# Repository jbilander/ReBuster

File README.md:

# ReBuster
A drop-in replacement PCB for the Amiga Super Buster chip

This is WORK IN PROGRESS. If you generate gerbers and order PCBs from this source you are doing so completely at your own risk!.

***

***

<br />

<br />

***

***

BOM Rev. 2A
---------
Reference  | Name/Value   | Package | Notes
-|-|-|-|
U1 | 10M04SCU169C8G  | BGA-169 11.0x11.0mm_Layout13x13 | Max 10 FPGA [10M04SCU169C8G](https://www.mouser.com/ProductDetail/989-10M04SCU169C8G)
U2 | LM1117-3.3 | SOT-223 | Low-Dropout Linear Regulator 3.3 Volt
U3,U5,U6 | SN74CBTD16210 | TSSOP-48 6.1x12.5mm_P0.5mm | 20-BIT FET Bus switch with level shifting, high-speed TTL-compatible. [74CBTD16210DGGR](https://www.mouser.com/ProductDetail/595-74CBTD16210DGGR)
U4 | SN74LVC16245ADGVR | TSSOP-48_4.4x9.7mm_P0.4mm | 16-bit (dual-octal) noninverting bus transceiver [SN74LVC16245ADGVR](https://www.mouser.com/ProductDetail/595-SNLVC16245ADGVR)
U7 | 74LVC2G07GV | TSOP-6_1.65x3.05mm_P0.95mm | Open Drain noninverting line driver [74LVC2G07GV](https://www.mouser.com/ProductDetail/771-LVC2G07GV125)
U8 | Winslow PLCC-84 Plug | PLCC-84 Plug | Optionally use a home made plug (stacked PCBs)
U9 | PLCC-84_TH_pin_holes | TH_plug_pins | Pins that could be used with the DIY-plug PCBs rev1d for manual fitting, L8.7mm [Aliexpress](https://www.aliexpress.com/item/32893608810.html).
RN1, RN2 | CAY16-1002F4LF RES ARRAY 4 Resistors 10k Ω | 1206 | [CAY16-1002F4LF](https://www.mouser.com/ProductDetail/652-CAY16-1002F4LF)
C1-3 | Capacitor 10uF | 1206 | 
C4,C5,C8,C11 | Capacitor 1uF | 0805 | 
C6,C7,C9,C10 | Capacitor 0.1uF = 100nF | 0805 | 
C12-C19, C21-C23 | Capacitor 0.01uF = 10nF | 0603 |
C20, C24-C28 | Capacitor 0.1uF = 100nF | 0603 |
JTAG | SMT Pin Header Male | SMT 2 x 5 Pin 2.0mm pitch |

***

***

***

BOM Rev. 1A
---------
Reference  | Name/Value   | Package | Notes
-|-|-|-|
U1 | GW1N-UV9UG169C6/I5  | BGA-169 11.0x11.0mm_Layout13x13 | Gowin FPGA [GW1N-UV9UG169](https://www.mouser.com/ProductDetail/192-GW1NUV9UG169C6I5)
U2 | LM1117-3.3 | SOT-223 | Low-Dropout Linear Regulator 3.3 Volt
U3-U6 | SN74CBTD16210 | TSSOP-48 6.1x12.5mm_P0.5mm | 20-BIT FET Bus switch with level shifting, high-speed TTL-compatible. [74CBTD16210DGGR](https://www.mouser.com/ProductDetail/595-74CBTD16210DGGR)
U7 | Winslow PLCC-84 Plug | PLCC-84 Plug | Optionally use a home made plug (stacked PCBs)
U8 | PLCC-84_TH_pin_holes | TH_plug_pins | Pins that could be used with the DIY-plug PCBs rev1d for manual fitting, L8.7mm [Aliexpress](https://www.aliexpress.com/item/32893608810.html).
RN1, RN2 | CAY16A-4701F4LF RES ARRAY 4 Resistors 4.7k Ω | 1206 | [CAY16A-4701F4LF](https://wwww.mouser.com/ProductDetail/652-CAY16A-4701F4LF)
C1-3 | Capacitor 10uF | 1206 | 
C4,C5,C8,C11 | Capacitor 1uF | 0805 | 
C6,C7,C9,C10 | Capacitor 0.1uF = 100nF | 0805 | 
C12-C19 | Capacitor 0.01uF = 10nF | 0603 |
C20 | Capacitor 0.1uF = 100nF | 0603 |
C21-C24 | Capacitor 0.01uF = 10nF | 0603 |
JTAG | SMT Pin Header Male | SMT 2 x 5 Pin 2.0mm pitch |

***

When ordering from JLCPCB select:

Specify Layer Sequence: Yes

    L1(Top layer):    F_Cu.gbr
    L2(Inner layer1): GND_Cu.gbr
    L3(Inner layer2): VCC_Cu.gbr
    L4(Bottom layer): B_Cu.gbr

Remove Order Number: 

    Specify a location

This will notify JLC where to put the order number, they will replace the "JLCJLCJLCJLC" silkscreen label.

***

[![CC BY-SA 4.0][cc-by-sa-shield]][cc-by-sa]

This work is licensed under a
[Creative Commons Attribution-ShareAlike 4.0 International License][cc-by-sa].

[![CC BY-SA 4.0][cc-by-sa-image]][cc-by-sa]

[cc-by-sa]: http://creativecommons.org/licenses/by-sa/4.0/
[cc-by-sa-image]: https://licensebuttons.net/l/by-sa/4.0/88x31.png
[cc-by-sa-shield]: https://img.shields.io/badge/License-CC%20BY--SA%204.0-lightgrey.svg

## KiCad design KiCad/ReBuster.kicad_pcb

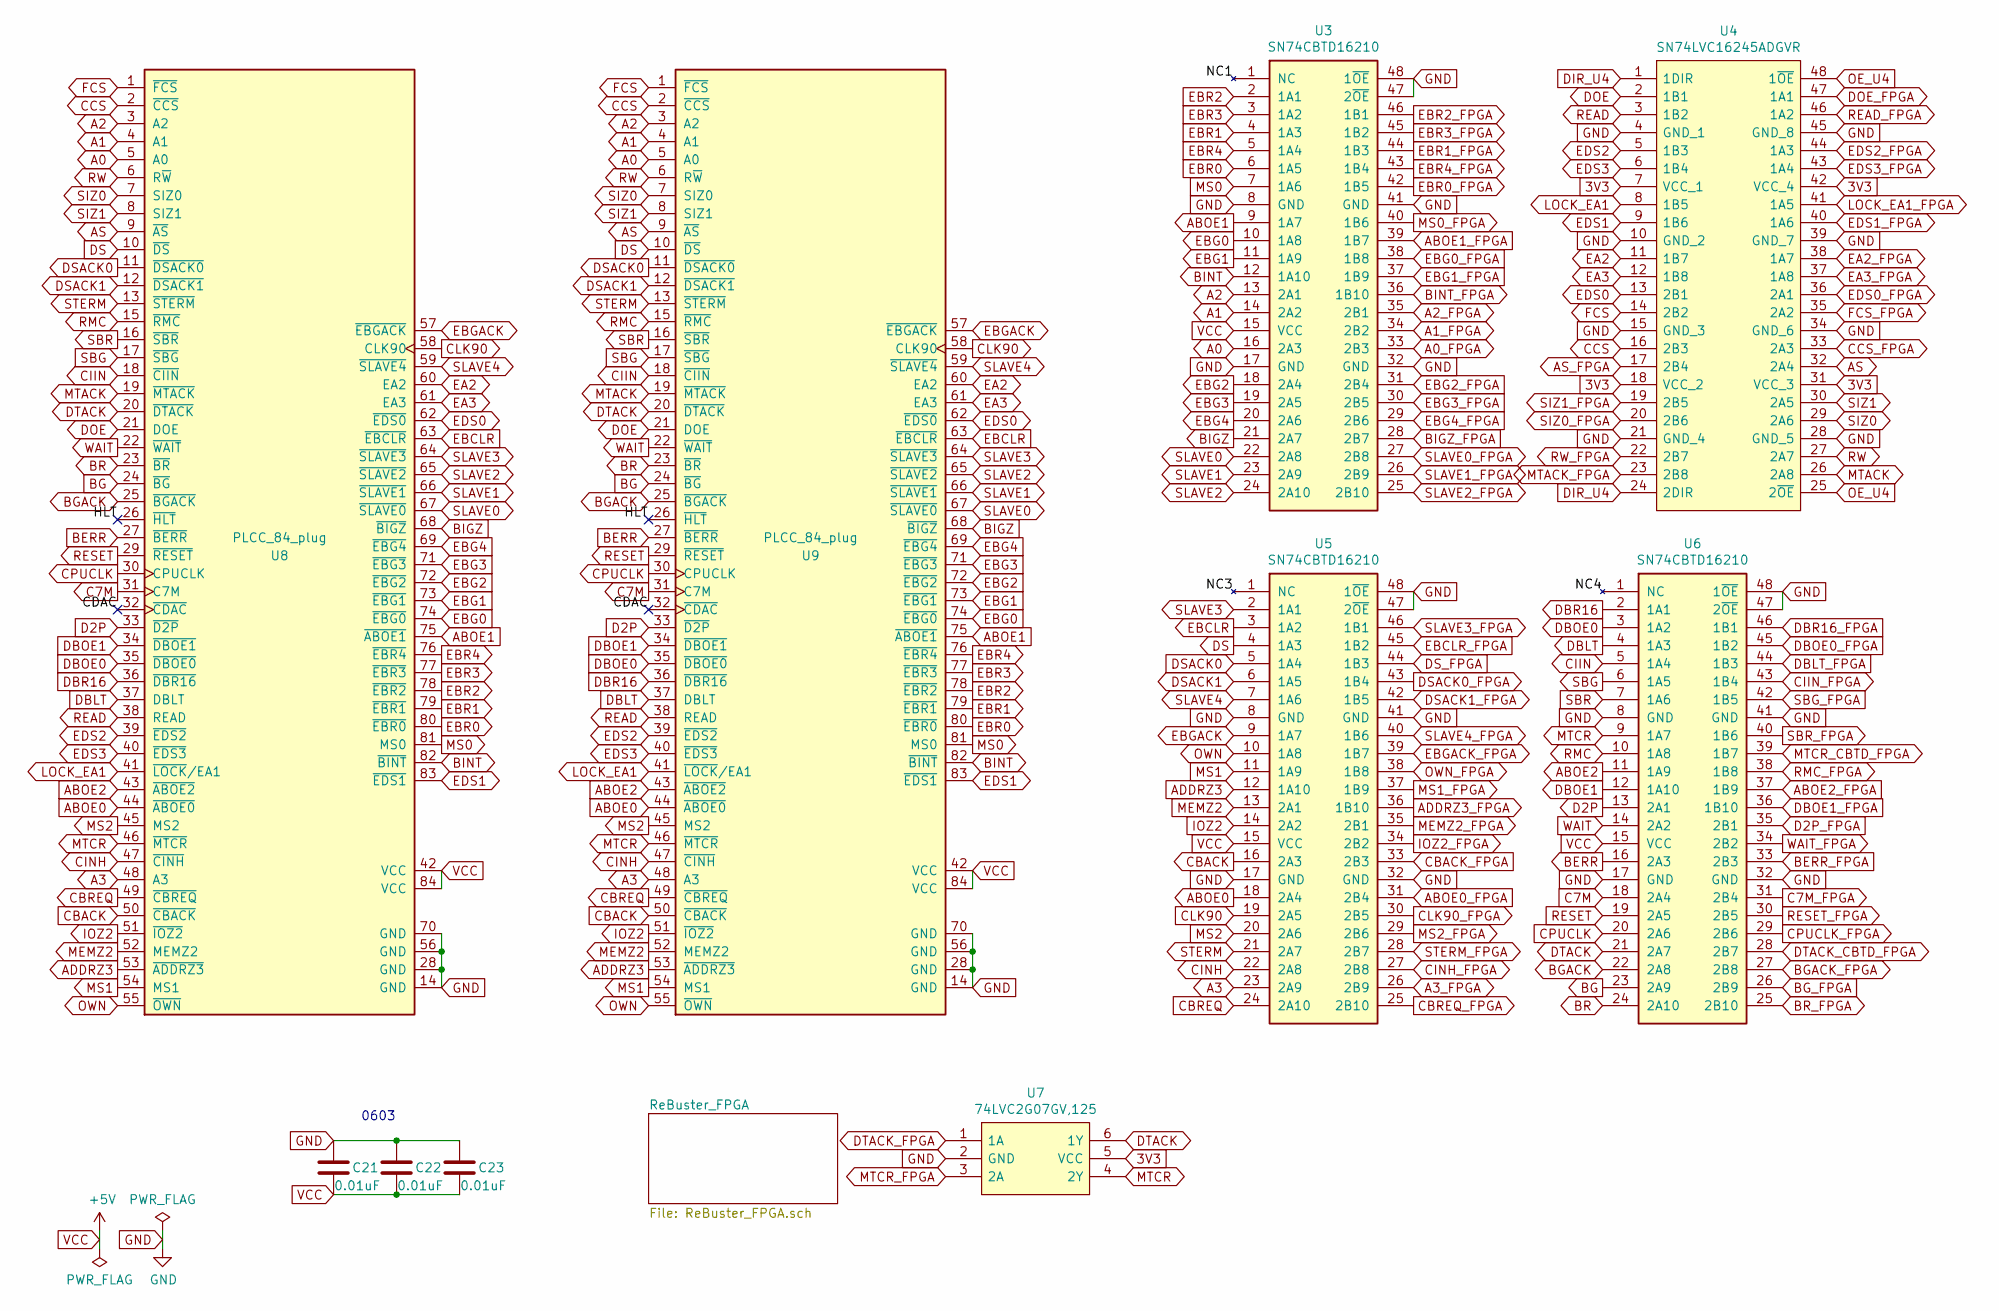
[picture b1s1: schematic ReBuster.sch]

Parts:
C21, C22, C23: 0.01uF; C_0603_1608Metric_Pad1.05x0.95mm_HandSolder
U3, U5, U6: SN74CBTD16210; TSSOP-48_6.1x12.5mm_P0.5mm_padLength_1mm
U4: SN74LVC16245ADGVR; TSSOP-48_4.4x9.7mm_P0.4mm_custom
U7: 74LVC2G07GV,125; TSOP-6_1.65x3.05mm_P0.95mm
U8: PLCC_84_plug; PLCC-84_Plug_P1.27mm_mirrored
U9: PLCC_84_plug; PLCC-84_TH_pin_holes

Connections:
3V3: U4.7 (VCC_1), U4.18 (VCC_2), U4.31 (VCC_3), U4.42 (VCC_4), U7.5 (VCC); also elsewhere on the board
/CDAC: U8.32 (~CDAC), U9.32 (~CDAC)
/HLT: U8.26 (~HLT), U9.26 (~HLT)
/NC1: U3.1 (NC)
/NC3: U5.1 (NC)
/NC4: U6.1 (NC)
A0: U3.16 (2A3), U8.5 (A0), U9.5 (A0)
A0_FPGA: U3.33 (2B3); also elsewhere on the board
A1: U3.14 (2A2), U8.4 (A1), U9.4 (A1)
A1_FPGA: U3.34 (2B2); also elsewhere on the board
A2: U3.13 (2A1), U8.3 (A2), U9.3 (A2)
A2_FPGA: U3.35 (2B1); also elsewhere on the board
A3: U5.23 (2A9), U8.48 (A3), U9.48 (A3)
A3_FPGA: U5.26 (2B9); also elsewhere on the board
ABOE0: U5.18 (2A4), U8.44 (~ABOE0), U9.44 (~ABOE0)
ABOE0_FPGA: U5.31 (2B4); also elsewhere on the board
ABOE1: U3.9 (1A7), U8.75 (~ABOE1), U9.75 (~ABOE1)
ABOE1_FPGA: U3.39 (1B7); also elsewhere on the board
ABOE2: U6.11 (1A9), U8.43 (~ABOE2), U9.43 (~ABOE2)
ABOE2_FPGA: U6.37 (1B9); also elsewhere on the board
ADDRZ3: U5.12 (1A10), U8.53 (~ADDRZ3), U9.53 (~ADDRZ3)
ADDRZ3_FPGA: U5.36 (1B10); also elsewhere on the board
AS: U4.32 (2A4), U8.9 (~AS), U9.9 (~AS)
AS_FPGA: U4.17 (2B4); also elsewhere on the board
BERR: U6.16 (2A3), U8.27 (~BERR), U9.27 (~BERR)
BERR_FPGA: U6.33 (2B3); also elsewhere on the board
BG: U6.23 (2A9), U8.24 (~BG), U9.24 (~BG)
BGACK: U6.22 (2A8), U8.25 (~BGACK), U9.25 (~BGACK)
BGACK_FPGA: U6.27 (2B8); also elsewhere on the board
BG_FPGA: U6.26 (2B9); also elsewhere on the board
BIGZ: U3.21 (2A7), U8.68 (~BIGZ), U9.68 (~BIGZ)
BIGZ_FPGA: U3.28 (2B7); also elsewhere on the board
BINT: U3.12 (1A10), U8.82 (~BINT), U9.82 (~BINT)
BINT_FPGA: U3.36 (1B10); also elsewhere on the board
BR: U6.24 (2A10), U8.23 (~BR), U9.23 (~BR)
BR_FPGA: U6.25 (2B10); also elsewhere on the board
C7M: U6.18 (2A4), U8.31 (C7M), U9.31 (C7M)
C7M_FPGA: U6.31 (2B4); also elsewhere on the board
CBACK: U5.16 (2A3), U8.50 (~CBACK), U9.50 (~CBACK)
CBACK_FPGA: U5.33 (2B3); also elsewhere on the board
CBREQ: U5.24 (2A10), U8.49 (~CBREQ), U9.49 (~CBREQ)
CBREQ_FPGA: U5.25 (2B10); also elsewhere on the board
CCS: U4.16 (2B3), U8.2 (~CCS), U9.2 (~CCS)
CCS_FPGA: U4.33 (2A3); also elsewhere on the board
CIIN: U6.5 (1A4), U8.18 (~CIIN), U9.18 (~CIIN)
CIIN_FPGA: U6.43 (1B4); also elsewhere on the board
CINH: U5.22 (2A8), U8.47 (~CINH), U9.47 (~CINH)
CINH_FPGA: U5.27 (2B8); also elsewhere on the board
CLK90: U5.19 (2A5), U8.58 (CLK90), U9.58 (CLK90)
CLK90_FPGA: U5.30 (2B5); also elsewhere on the board
CPUCLK: U6.20 (2A6), U8.30 (CPUCLK), U9.30 (CPUCLK)
CPUCLK_FPGA: U6.29 (2B6); also elsewhere on the board
D2P: U6.13 (2A1), U8.33 (~D2P), U9.33 (~D2P)
D2P_FPGA: U6.35 (2B1); also elsewhere on the board
DBLT: U6.4 (1A3), U8.37 (DBLT), U9.37 (DBLT)
DBLT_FPGA: U6.44 (1B3); also elsewhere on the board
DBOE0: U6.3 (1A2), U8.35 (~DBOE0), U9.35 (~DBOE0)
DBOE0_FPGA: U6.45 (1B2); also elsewhere on the board
DBOE1: U6.12 (1A10), U8.34 (~DBOE1), U9.34 (~DBOE1)
DBOE1_FPGA: U6.36 (1B10); also elsewhere on the board
DBR16: U6.2 (1A1), U8.36 (~DBR16), U9.36 (~DBR16)
DBR16_FPGA: U6.46 (1B1); also elsewhere on the board
DIR_U4: U4.1 (1DIR), U4.24 (2DIR); also elsewhere on the board
DOE: U4.2 (1B1), U8.21 (DOE), U9.21 (DOE)
DOE_FPGA: U4.47 (1A1); also elsewhere on the board
DS: U5.4 (1A3), U8.10 (~DS), U9.10 (~DS)
DSACK0: U5.5 (1A4), U8.11 (~DSACK0), U9.11 (~DSACK0)
DSACK0_FPGA: U5.43 (1B4); also elsewhere on the board
DSACK1: U5.6 (1A5), U8.12 (~DSACK1), U9.12 (~DSACK1)
DSACK1_FPGA: U5.42 (1B5); also elsewhere on the board
DS_FPGA: U5.44 (1B3); also elsewhere on the board
DTACK: U6.21 (2A7), U7.6 (1Y), U8.20 (~DTACK), U9.20 (~DTACK)
DTACK_CBTD_FPGA: U6.28 (2B7); also elsewhere on the board
DTACK_FPGA: U7.1 (1A); also elsewhere on the board
EA2: U4.11 (1B7), U8.60 (EA2), U9.60 (EA2)
EA2_FPGA: U4.38 (1A7); also elsewhere on the board
EA3: U4.12 (1B8), U8.61 (EA3), U9.61 (EA3)
EA3_FPGA: U4.37 (1A8); also elsewhere on the board
EBCLR: U5.3 (1A2), U8.63 (~EBCLR), U9.63 (~EBCLR)
EBCLR_FPGA: U5.45 (1B2); also elsewhere on the board
EBG0: U3.10 (1A8), U8.74 (~EBG0), U9.74 (~EBG0)
EBG0_FPGA: U3.38 (1B8); also elsewhere on the board
EBG1: U3.11 (1A9), U8.73 (~EBG1), U9.73 (~EBG1)
EBG1_FPGA: U3.37 (1B9); also elsewhere on the board
EBG2: U3.18 (2A4), U8.72 (~EBG2), U9.72 (~EBG2)
EBG2_FPGA: U3.31 (2B4); also elsewhere on the board
EBG3: U3.19 (2A5), U8.71 (~EBG3), U9.71 (~EBG3)
EBG3_FPGA: U3.30 (2B5); also elsewhere on the board
EBG4: U3.20 (2A6), U8.69 (~EBG4), U9.69 (~EBG4)
EBG4_FPGA: U3.29 (2B6); also elsewhere on the board
EBGACK: U5.9 (1A7), U8.57 (~EBGACK), U9.57 (~EBGACK)
EBGACK_FPGA: U5.39 (1B7); also elsewhere on the board
EBR0: U3.6 (1A5), U8.80 (~EBR0), U9.80 (~EBR0)
EBR0_FPGA: U3.42 (1B5); also elsewhere on the board
EBR1: U3.4 (1A3), U8.79 (~EBR1), U9.79 (~EBR1)
EBR1_FPGA: U3.44 (1B3); also elsewhere on the board
EBR2: U3.2 (1A1), U8.78 (~EBR2), U9.78 (~EBR2)
EBR2_FPGA: U3.46 (1B1); also elsewhere on the board
EBR3: U3.3 (1A2), U8.77 (~EBR3), U9.77 (~EBR3)
EBR3_FPGA: U3.45 (1B2); also elsewhere on the board
EBR4: U3.5 (1A4), U8.76 (~EBR4), U9.76 (~EBR4)
EBR4_FPGA: U3.43 (1B4); also elsewhere on the board
EDS0: U4.13 (2B1), U8.62 (~EDS0), U9.62 (~EDS0)
EDS0_FPGA: U4.36 (2A1); also elsewhere on the board
EDS1: U4.9 (1B6), U8.83 (~EDS1), U9.83 (~EDS1)
EDS1_FPGA: U4.40 (1A6); also elsewhere on the board
EDS2: U4.5 (1B3), U8.39 (~EDS2), U9.39 (~EDS2)
EDS2_FPGA: U4.44 (1A3); also elsewhere on the board
EDS3: U4.6 (1B4), U8.40 (~EDS3), U9.40 (~EDS3)
EDS3_FPGA: U4.43 (1A4); also elsewhere on the board
FCS: U4.14 (2B2), U8.1 (~FCS), U9.1 (~FCS)
FCS_FPGA: U4.35 (2A2); also elsewhere on the board
GND: C21.1, C22.1, C23.1, U3.8 (GND), U3.17 (GND), U3.32 (GND), U3.41 (GND), U3.47 (2~OE), U3.48 (1~OE), U4.4 (GND_1), U4.10 (GND_2), U4.15 (GND_3), U4.21 (GND_4), U4.28 (GND_5), U4.34 (GND_6), U4.39 (GND_7), U4.45 (GND_8), U5.8 (GND), U5.17 (GND), U5.32 (GND), U5.41 (GND), U5.47 (2~OE), U5.48 (1~OE), U6.8 (GND), U6.17 (GND), U6.32 (GND), U6.41 (GND), U6.47 (2~OE), U6.48 (1~OE), U7.2 (GND), U8.14 (GND), U8.28 (GND), U8.56 (GND), U8.70 (GND), U9.14 (GND), U9.28 (GND), U9.56 (GND), U9.70 (GND); also elsewhere on the board
IOZ2: U5.14 (2A2), U8.51 (~IOZ2), U9.51 (~IOZ2)
IOZ2_FPGA: U5.34 (2B2); also elsewhere on the board
LOCK_EA1: U4.8 (1B5), U8.41 (~LOCK~/EA1), U9.41 (~LOCK~/EA1)
LOCK_EA1_FPGA: U4.41 (1A5); also elsewhere on the board
MEMZ2: U5.13 (2A1), U8.52 (MEMZ2), U9.52 (MEMZ2)
MEMZ2_FPGA: U5.35 (2B1); also elsewhere on the board
MS0: U3.7 (1A6), U8.81 (MS0), U9.81 (MS0)
MS0_FPGA: U3.40 (1B6); also elsewhere on the board
MS1: U5.11 (1A9), U8.54 (MS1), U9.54 (MS1)
MS1_FPGA: U5.37 (1B9); also elsewhere on the board
MS2: U5.20 (2A6), U8.45 (MS2), U9.45 (MS2)
MS2_FPGA: U5.29 (2B6); also elsewhere on the board
MTACK: U4.26 (2A8), U8.19 (~MTACK), U9.19 (~MTACK)
MTACK_FPGA: U4.23 (2B8); also elsewhere on the board
MTCR: U6.9 (1A7), U7.4 (2Y), U8.46 (~MTCR), U9.46 (~MTCR)
MTCR_CBTD_FPGA: U6.39 (1B7); also elsewhere on the board
MTCR_FPGA: U7.3 (2A); also elsewhere on the board
OE_U4: U4.25 (2~OE), U4.48 (1~OE); also elsewhere on the board
OWN: U5.10 (1A8), U8.55 (~OWN), U9.55 (~OWN)
OWN_FPGA: U5.38 (1B8); also elsewhere on the board
READ: U4.3 (1B2), U8.38 (READ), U9.38 (READ)
READ_FPGA: U4.46 (1A2); also elsewhere on the board
RESET: U6.19 (2A5), U8.29 (~RESET), U9.29 (~RESET)
RESET_FPGA: U6.30 (2B5); also elsewhere on the board
RMC: U6.10 (1A8), U8.15 (~RMC), U9.15 (~RMC)
RMC_FPGA: U6.38 (1B8); also elsewhere on the board
RW: U4.27 (2A7), U8.6 (R~W), U9.6 (R~W)
RW_FPGA: U4.22 (2B7); also elsewhere on the board
SBG: U6.6 (1A5), U8.17 (~SBG), U9.17 (~SBG)
SBG_FPGA: U6.42 (1B5); also elsewhere on the board
SBR: U6.7 (1A6), U8.16 (~SBR), U9.16 (~SBR)
SBR_FPGA: U6.40 (1B6); also elsewhere on the board
SIZ0: U4.29 (2A6), U8.7 (SIZ0), U9.7 (SIZ0)
SIZ0_FPGA: U4.20 (2B6); also elsewhere on the board
SIZ1: U4.30 (2A5), U8.8 (SIZ1), U9.8 (SIZ1)
SIZ1_FPGA: U4.19 (2B5); also elsewhere on the board
SLAVE0: U3.22 (2A8), U8.67 (~SLAVE0), U9.67 (~SLAVE0)
SLAVE0_FPGA: U3.27 (2B8); also elsewhere on the board
SLAVE1: U3.23 (2A9), U8.66 (~SLAVE1), U9.66 (~SLAVE1)
SLAVE1_FPGA: U3.26 (2B9); also elsewhere on the board
SLAVE2: U3.24 (2A10), U8.65 (~SLAVE2), U9.65 (~SLAVE2)
SLAVE2_FPGA: U3.25 (2B10); also elsewhere on the board
SLAVE3: U5.2 (1A1), U8.64 (~SLAVE3), U9.64 (~SLAVE3)
SLAVE3_FPGA: U5.46 (1B1); also elsewhere on the board
SLAVE4: U5.7 (1A6), U8.59 (~SLAVE4), U9.59 (~SLAVE4)
SLAVE4_FPGA: U5.40 (1B6); also elsewhere on the board
STERM: U5.21 (2A7), U8.13 (~STERM), U9.13 (~STERM)
STERM_FPGA: U5.28 (2B7); also elsewhere on the board
VCC: C21.2, C22.2, C23.2, U3.15 (VCC), U5.15 (VCC), U6.15 (VCC), U8.42 (VCC), U8.84 (VCC), U9.42 (VCC), U9.84 (VCC); also elsewhere on the board
WAIT: U6.14 (2A2), U8.22 (~WAIT), U9.22 (~WAIT)
WAIT_FPGA: U6.34 (2B2); also elsewhere on the board

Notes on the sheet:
0603

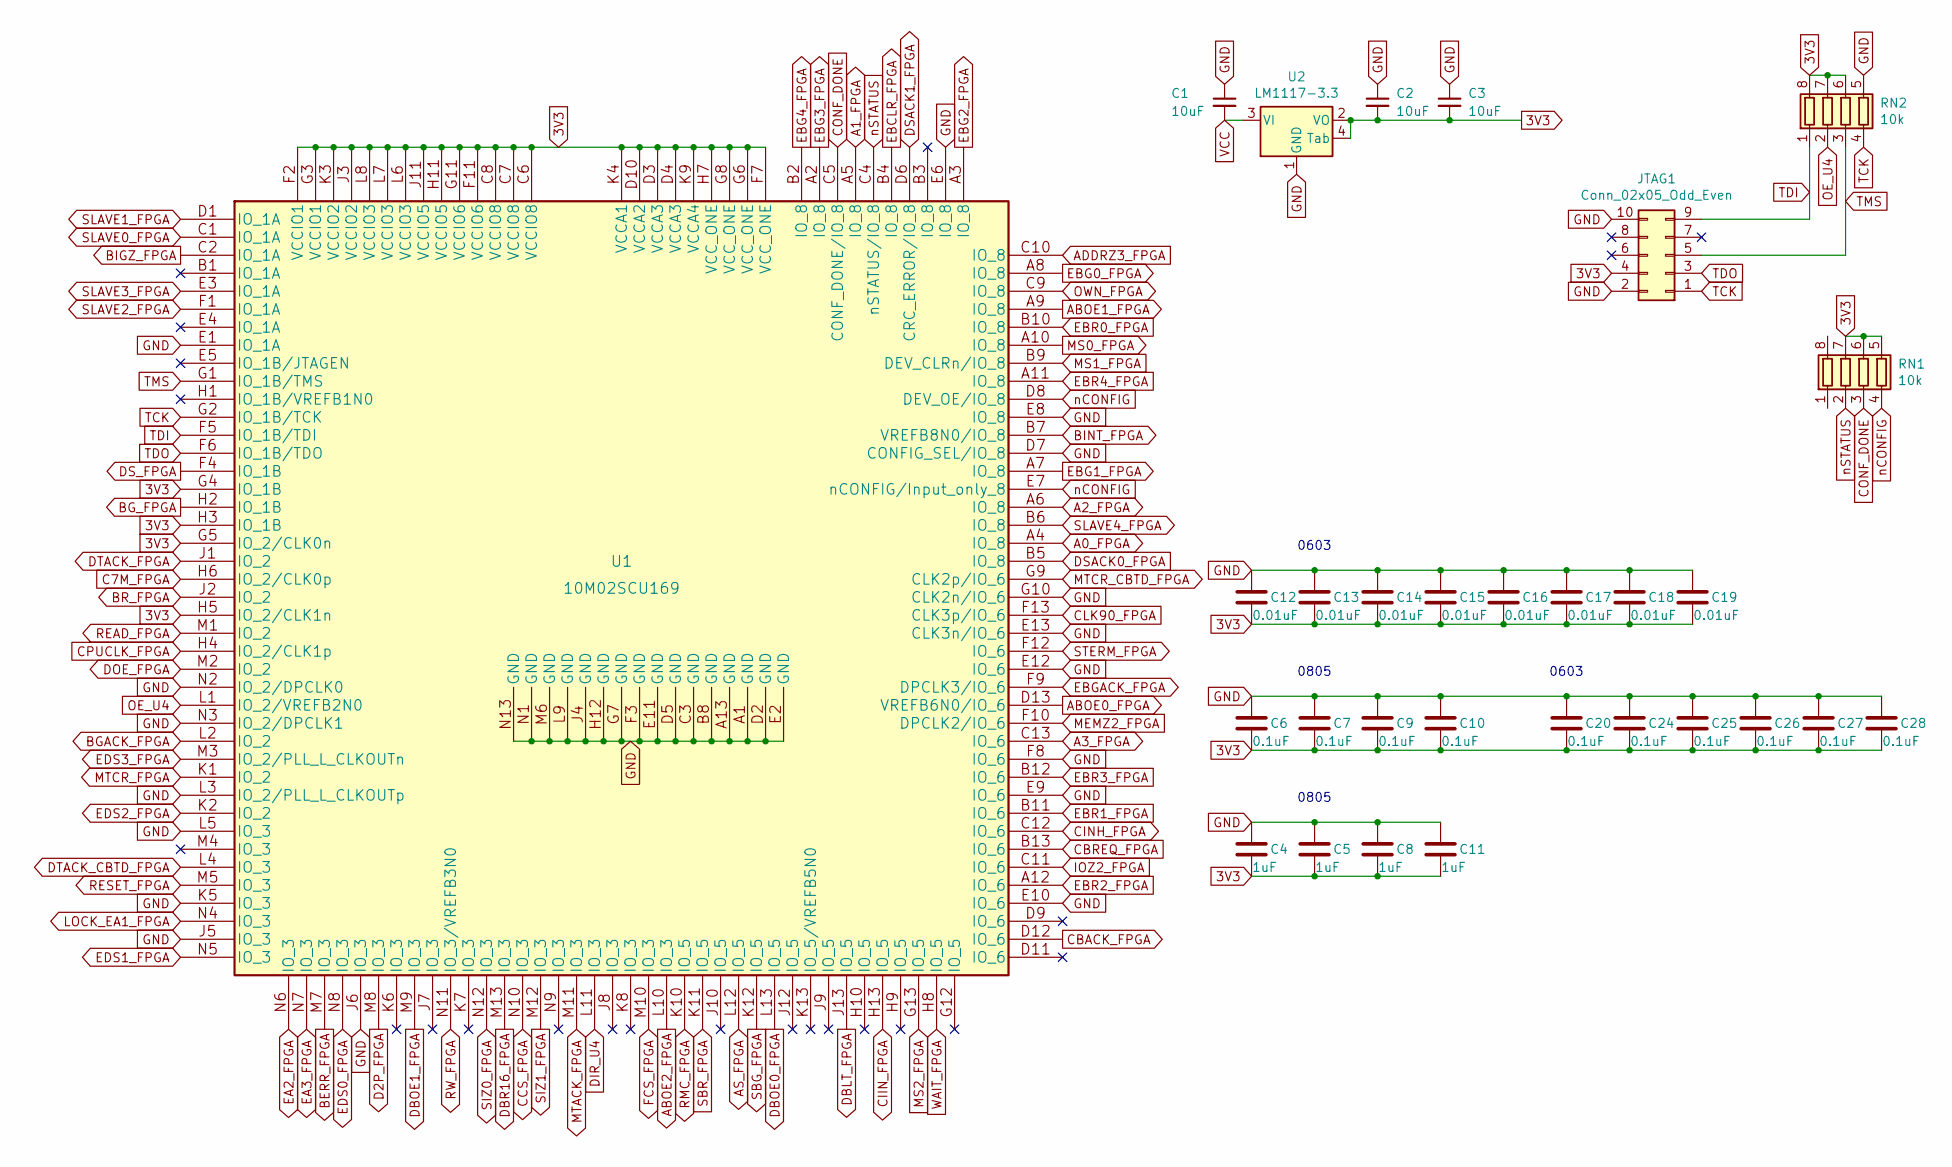
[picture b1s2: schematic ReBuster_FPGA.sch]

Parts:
C1, C2, C3: 10uF; C_1206_3216Metric_Pad1.42x1.75mm_HandSolder
C4, C5, C8, C11: 1uF; C_0805_2012Metric_Pad1.15x1.40mm_HandSolder
C6, C7, C9, C10: 0.1uF; C_0805_2012Metric_Pad1.15x1.40mm_HandSolder
C12, C13, C14, C15, C16, C17, C19: 0.01uF; C_0603_1608Metric_Pad1.05x0.95mm_HandSolder
C18: 0.01uF; C_0603_1608Metric
C20: 0.1uF; C_0603_1608Metric_Pad1.05x0.95mm_HandSolder
C24, C25, C28: 0.1uF; C_0603_1608Metric_Pad1.05x0.95mm_HandSolder_extended
C26, C27: 0.1uF; C_0603_1608Metric_Pad1.08x0.95mm_HandSolder
JTAG1: Conn_02x05_Odd_Even; PinHeader_2x05_P2.00mm_Vertical_SMD
RN1, RN2: 10k; RESCAF80P320X160X60-8N
U1: 10M02SCU169; BGA-169_11.0x11.0mm_Layout13x13_P0.8mm_Ball0.5mm_Pad0.35mm_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
U2: LM1117-3.3; SOT-223

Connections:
3V3: C2.2, C3.2, C4.2, C5.2, C6.2, C7.2, C8.2, C9.2, C10.2, C11.2, C12.2, C13.2, C14.2, C15.2, C16.2, C17.2, C18.2, C19.2, C20.2, C24.2, C25.2, C26.2, C27.2, C28.2, JTAG1.4, RN1.5 (R4.2), RN1.6 (R3.2), RN1.7 (R2.2), RN2.6 (R3.2), RN2.7 (R2.2), RN2.8 (R1.2), U1.C6 (VCCIO8), U1.C7 (VCCIO8), U1.C8 (VCCIO8), U1.D3 (VCCA3), U1.D4 (VCCA3), U1.D10 (VCCA2), U1.F2 (VCCIO1), U1.F7 (VCC_ONE), U1.F11 (VCCIO6), U1.G3 (VCCIO1), U1.G4 (IO_1B), U1.G5 (IO_2/CLK0n), U1.G6 (VCC_ONE), U1.G8 (VCC_ONE), U1.G11 (VCCIO6), U1.H3 (IO_1B), U1.H5 (IO_2/CLK1n), U1.H7 (VCC_ONE), U1.H11 (VCCIO5), U1.J3 (VCCIO2), U1.J11 (VCCIO5), U1.K3 (VCCIO2), U1.K4 (VCCA1), U1.K9 (VCCA4), U1.L6 (VCCIO3), U1.L7 (VCCIO3), U1.L8 (VCCIO3), U2.2 (VO), U2.4 (Tab); also elsewhere on the board
A0_FPGA: U1.A4 (IO_8); also elsewhere on the board
A1_FPGA: U1.A5 (IO_8); also elsewhere on the board
A2_FPGA: U1.A6 (IO_8); also elsewhere on the board
A3_FPGA: U1.C13 (IO_6); also elsewhere on the board
ABOE0_FPGA: U1.D13 (VREFB6N0/IO_6); also elsewhere on the board
ABOE1_FPGA: U1.A9 (IO_8); also elsewhere on the board
ABOE2_FPGA: U1.L10 (IO_3); also elsewhere on the board
ADDRZ3_FPGA: U1.C10 (IO_8); also elsewhere on the board
AS_FPGA: U1.L12 (IO_5); also elsewhere on the board
BERR_FPGA: U1.M7 (IO_3); also elsewhere on the board
BGACK_FPGA: U1.L2 (IO_2); also elsewhere on the board
BG_FPGA: U1.H2 (IO_1B); also elsewhere on the board
BIGZ_FPGA: U1.C2 (IO_1A); also elsewhere on the board
BINT_FPGA: U1.B7 (VREFB8N0/IO_8); also elsewhere on the board
BR_FPGA: U1.J2 (IO_2); also elsewhere on the board
C7M_FPGA: U1.H6 (IO_2/CLK0p); also elsewhere on the board
CBACK_FPGA: U1.D12 (IO_6); also elsewhere on the board
CBREQ_FPGA: U1.B13 (IO_6); also elsewhere on the board
CCS_FPGA: U1.N10 (IO_3); also elsewhere on the board
CIIN_FPGA: U1.H13 (IO_5); also elsewhere on the board
CINH_FPGA: U1.C12 (IO_6); also elsewhere on the board
CLK90_FPGA: U1.F13 (CLK3p/IO_6); also elsewhere on the board
CONF_DONE: RN1.3 (R3.1), U1.C5 (CONF_DONE/IO_8)
CPUCLK_FPGA: U1.H4 (IO_2/CLK1p); also elsewhere on the board
D2P_FPGA: U1.M8 (IO_3); also elsewhere on the board
DBLT_FPGA: U1.J13 (IO_5); also elsewhere on the board
DBOE0_FPGA: U1.L13 (IO_5); also elsewhere on the board
DBOE1_FPGA: U1.M9 (IO_3); also elsewhere on the board
DBR16_FPGA: U1.M13 (IO_3); also elsewhere on the board
DIR_U4: U1.L11 (IO_3); also elsewhere on the board
DOE_FPGA: U1.M2 (IO_2); also elsewhere on the board
DSACK0_FPGA: U1.B5 (IO_8); also elsewhere on the board
DSACK1_FPGA: U1.D6 (CRC_ERROR/IO_8); also elsewhere on the board
DS_FPGA: U1.F4 (IO_1B); also elsewhere on the board
DTACK_CBTD_FPGA: U1.L4 (IO_3); also elsewhere on the board
DTACK_FPGA: U1.J1 (IO_2); also elsewhere on the board
EA2_FPGA: U1.N6 (IO_3); also elsewhere on the board
EA3_FPGA: U1.N7 (IO_3); also elsewhere on the board
EBCLR_FPGA: U1.B4 (IO_8); also elsewhere on the board
EBG0_FPGA: U1.A8 (IO_8); also elsewhere on the board
EBG1_FPGA: U1.A7 (IO_8); also elsewhere on the board
EBG2_FPGA: U1.A3 (IO_8); also elsewhere on the board
EBG3_FPGA: U1.A2 (IO_8); also elsewhere on the board
EBG4_FPGA: U1.B2 (IO_8); also elsewhere on the board
EBGACK_FPGA: U1.F9 (DPCLK3/IO_6); also elsewhere on the board
EBR0_FPGA: U1.B10 (IO_8); also elsewhere on the board
EBR1_FPGA: U1.B11 (IO_6); also elsewhere on the board
EBR2_FPGA: U1.A12 (IO_6); also elsewhere on the board
EBR3_FPGA: U1.B12 (IO_6); also elsewhere on the board
EBR4_FPGA: U1.A11 (IO_8); also elsewhere on the board
EDS0_FPGA: U1.N8 (IO_3); also elsewhere on the board
EDS1_FPGA: U1.N5 (IO_3); also elsewhere on the board
EDS2_FPGA: U1.K2 (IO_2); also elsewhere on the board
EDS3_FPGA: U1.M3 (IO_2/PLL_L_CLKOUTn); also elsewhere on the board
FCS_FPGA: U1.M10 (IO_3); also elsewhere on the board
GND: C1.1, C2.1, C3.1, C4.1, C5.1, C6.1, C7.1, C8.1, C9.1, C10.1, C11.1, C12.1, C13.1, C14.1, C15.1, C16.1, C17.1, C18.1, C19.1, C20.1, C24.1, C25.1, C26.1, C27.1, C28.1, JTAG1.2, JTAG1.10, RN2.5 (R4.2), U1.A1 (GND), U1.A13 (GND), U1.B8 (GND), U1.C3 (GND), U1.D2 (GND), U1.D5 (GND), U1.D7 (CONFIG_SEL/IO_8), U1.E1 (IO_1A), U1.E2 (GND), U1.E6 (IO_8), U1.E8 (IO_8), U1.E9 (IO_6), U1.E10 (IO_6), U1.E11 (GND), U1.E12 (IO_6), U1.E13 (CLK3n/IO_6), U1.F3 (GND), U1.F8 (IO_6), U1.G7 (GND), U1.G10 (CLK2n/IO_6), U1.H12 (GND), U1.J4 (GND), U1.J5 (IO_3), U1.J6 (IO_3), U1.K5 (IO_3), U1.L3 (IO_2/PLL_L_CLKOUTp), U1.L5 (IO_3), U1.L9 (GND), U1.M6 (GND), U1.N1 (GND), U1.N2 (IO_2/DPCLK0), U1.N3 (IO_2/DPCLK1), U1.N13 (GND), U2.1 (GND); also elsewhere on the board
IOZ2_FPGA: U1.C11 (IO_6); also elsewhere on the board
LOCK_EA1_FPGA: U1.N4 (IO_3); also elsewhere on the board
MEMZ2_FPGA: U1.F10 (DPCLK2/IO_6); also elsewhere on the board
MS0_FPGA: U1.A10 (IO_8); also elsewhere on the board
MS1_FPGA: U1.B9 (DEV_CLRn/IO_8); also elsewhere on the board
MS2_FPGA: U1.G13 (IO_5); also elsewhere on the board
MTACK_FPGA: U1.M11 (IO_3); also elsewhere on the board
MTCR_CBTD_FPGA: U1.G9 (CLK2p/IO_6); also elsewhere on the board
MTCR_FPGA: U1.K1 (IO_2); also elsewhere on the board
OE_U4: RN2.2 (R2.1), U1.L1 (IO_2/VREFB2N0); also elsewhere on the board
OWN_FPGA: U1.C9 (IO_8); also elsewhere on the board
READ_FPGA: U1.M1 (IO_2); also elsewhere on the board
RESET_FPGA: U1.M5 (IO_3); also elsewhere on the board
RMC_FPGA: U1.K10 (IO_5); also elsewhere on the board
RW_FPGA: U1.N11 (IO_3/VREFB3N0); also elsewhere on the board
SBG_FPGA: U1.K12 (IO_5); also elsewhere on the board
SBR_FPGA: U1.K11 (IO_5); also elsewhere on the board
SIZ0_FPGA: U1.N12 (IO_3); also elsewhere on the board
SIZ1_FPGA: U1.M12 (IO_3); also elsewhere on the board
SLAVE0_FPGA: U1.C1 (IO_1A); also elsewhere on the board
SLAVE1_FPGA: U1.D1 (IO_1A); also elsewhere on the board
SLAVE2_FPGA: U1.F1 (IO_1A); also elsewhere on the board
SLAVE3_FPGA: U1.E3 (IO_1A); also elsewhere on the board
SLAVE4_FPGA: U1.B6 (IO_8); also elsewhere on the board
STERM_FPGA: U1.F12 (IO_6); also elsewhere on the board
TCK: JTAG1.1, RN2.4 (R4.1), U1.G2 (IO_1B/TCK)
TDI: JTAG1.9, RN2.1 (R1.1), U1.F5 (IO_1B/TDI)
TDO: JTAG1.3, U1.F6 (IO_1B/TDO)
TMS: JTAG1.5, RN2.3 (R3.1), U1.G1 (IO_1B/TMS)
VCC: C1.2, U2.3 (VI); also elsewhere on the board
WAIT_FPGA: U1.H8 (IO_5); also elsewhere on the board
nCONFIG: RN1.4 (R4.1), U1.D8 (DEV_OE/IO_8), U1.E7 (nCONFIG/Input_only_8)
nSTATUS: RN1.2 (R2.1), U1.C4 (nSTATUS/IO_8)

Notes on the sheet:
0603
0805

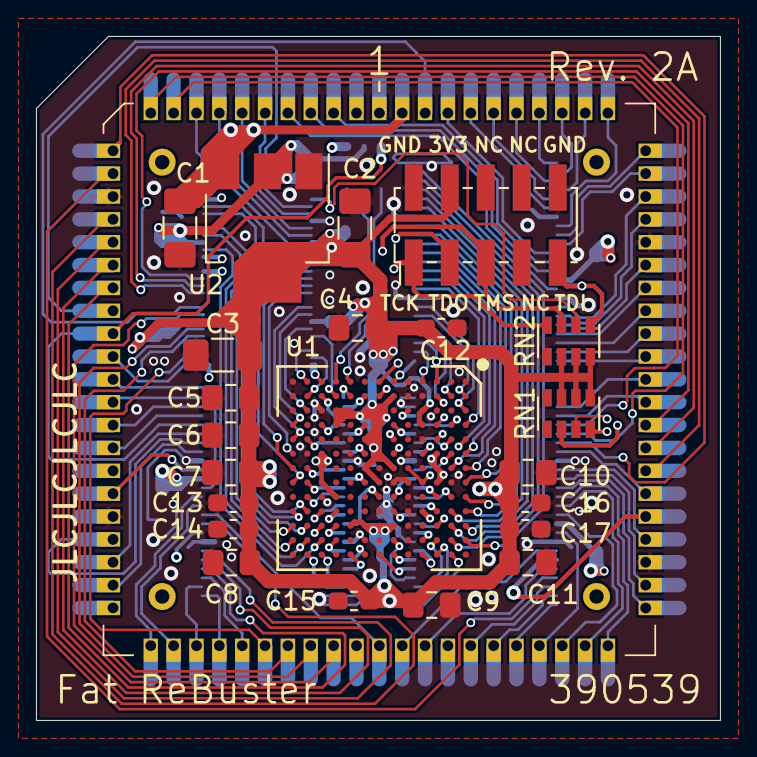
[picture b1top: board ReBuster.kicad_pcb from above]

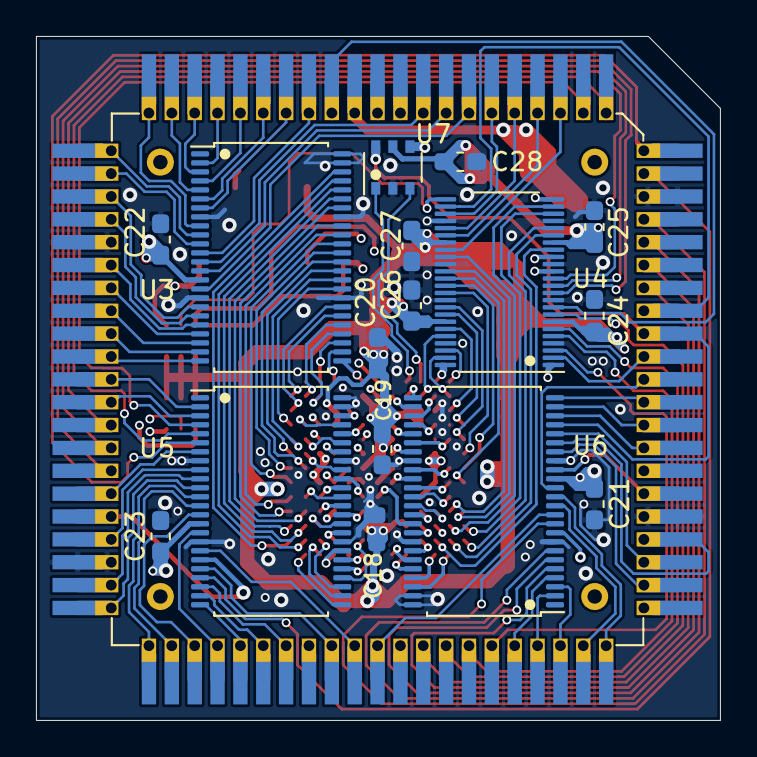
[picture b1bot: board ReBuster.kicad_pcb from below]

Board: 4 copper layers, 38.0 x 38.0 mm, 40 parts (17 on the bottom side), 168 nets.

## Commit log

2024-11-18 Add .gitignore file
2024-11-18 Add footprints
2024-11-18 Add 3D-models
2024-11-18 Add base skel of ReBuster based on ReSDMAC design
2024-11-18 Add license
2024-11-18 Add readme file
2024-11-19 Convert ReSDMAC symbol to ReBuster and removing symbols not used
2024-11-19 Adapted the design for Super Buster pinout, renamed all nets, assigned clk signals C7M,CPUCLK,CDAC,CLK90 to CLK0p,CLK1p,CLK2p,CLK3p, and re-routed where needed
2024-11-19 Corrected and verified direction assignment on all nets/pins and did some small routing fixes
2024-11-20 Silkscreen fixes on the CBTD footprints
2024-11-20 Add rev1a schematic pdf
2024-11-20 Add BOM
2024-11-20 Corrected link to 3D-models of DIY-plug PCBs
2024-11-20 Add screenshot images
2024-12-20 Fix show U3,U4,U5,U6 references on silkscreen
2024-12-25 add images
2025-01-19 small GND fix improvement for C22,C24 adding a second GND via
2025-01-28 small routing improvement
2025-03-21 Change RN1, RN2 value from 10k to 4.7k (CAY16A-4701F4LF) to follow Gowin JTAG recommended design.
2025-03-22 Add symbol for Gowin FPGA GW1N-UV9UG169
2025-03-22 Change U1 from 10M02SCU169C8G to pin compatible Gowin FPGA GW1N-UV9UG169C6/I5
2025-03-22 Add pdf schematic rev. 1a
2025-04-01 deleted file
2026-02-22 update footprint
2026-02-22 Change back to a 10M02SCU169 FPGA
2026-02-22 replace U4 (SN74CBTD16210) with a SN74LVC16T245DGVR
2026-02-22 Fix pad size on U4 footprint
2026-02-23 Add 74LVC2T45DC for handling DTACKn and MTACKn
2026-02-23 Route AS,SIZ1,SIZ0,RW to U4 (SN74LVC16T245DGVR) and FPGA
2026-02-23 Route EDS1, CCS, FCS signals to U4 (SN74LVC16T245DGVR) and FPGA
2026-02-24 Relocate A0,A1,A2 to FPGA pin A4,A5,A6 and route traces
2026-02-24 Remove JP1 and assign its pull-up resistor to OE_U4
2026-02-24 Add pull-down resistor to DIR_U7 and assign N9-pin and route trace
2026-02-24 Route DOE to U4 (SN74LVC16T245DGVR) change J1 -> M2 in FPGA
2026-02-24 Add 0.6 x 0.3 mm via
2026-02-24 Route READ to U4 (SN74LVC16T245DGVR) change H13 -> M1 in FPGA
2026-02-24 Route STERM change N10 -> F12 in FPGA
2026-02-24 Route EDS2 to U4 (SN74LVC16T245DGVR) change K13 -> K2 in FPGA
2026-02-24 Route EDS3 to U4 (SN74LVC16T245DGVR) change K12 -> M3 in FPGA
2026-02-24 Route EA1_LOCK to U4 (SN74LVC16T245DGVR) change K10 -> N4 in FPGA
2026-02-24 Route MTCR to U4 (SN74LVC16T245DGVR) change F12 -> N5 in FPGA
2026-02-25 Route EA2,EA3 to U4 (SN74LVC16T245DGVR) change D6 -> N6, B5 -> N7 in FPGA
2026-02-25 Route EDS0 to U4 (SN74LVC16T245DGVR) change F4 -> N8 in FPGA
2026-02-25 Route RMC, SBR, SBG, CIIN to U6 (SN74CBTD16210) and assign pins K10, K11, K12, H13 in FPGA respectively
2026-02-25 small routing fixes upgrading 0.45/0.2 mm vias to 0.5/0.3 mm where possible
2026-02-25 Change resistor networks (RN1,RN2) to 10k Ohm
2026-02-25 Add 0603 modified cap footprint
2026-02-25 Add VCC cap for U7 (74LVC2T45DC)
2026-02-25 Add two caps for 3.3v input pins on U4 (SN74LVC16T245DGVR)
2026-02-25 Route 3.3v to U4 via caps and optimize via placements
2026-02-26 Silkscreen fixes
2026-02-26 Silkscreen fix, indicate pin 1 with a dot on U4 and U7
2026-03-01 remove CDAC clock (not used) and put /MTCR signal there
2026-03-01 remove HLT-signal (not used) and put /DTACK signal there
2026-03-02 Replace 74LVC2T45DC with 74LVC2G07GV and prepare rerouting, reroute /DTACK
2026-03-02 Relocate EDS1 signal to replace MTCR's position (pin 9 and 40) in SN74LVC16T245
2026-03-02 Add footprint
2026-03-02 Add symbol for SN74LVC16245ADGVR
2026-03-02 Replace SN74LVC16T245DGVR with SN74LVC16245ADGVR and fix caps C24,C25 to instead be connected to 3V3
2026-03-02 Assign MTACK to pin 23,26 in SN74LVC16245 and M11 in FPGA and route trace
2026-03-02 Assign RW to pin 22,27 in SN74LVC16245 and route trace
2026-03-02 Assign SIZ0 to pin 20,29 in SN74LVC16245 and route trace
2026-03-02 Assign SIZ1 to pin 19,30 in SN74LVC16245 and M12 in FPGA and route trace
2026-03-02 Assign AS to pin 17,32 in SN74LVC16245 and L12 in FPGA and route trace
2026-03-02 Some small power routing improvements and via positioning
2026-03-02 Change C18 from handsolder footprint to normal
2026-03-03 Small silkscreen fixes, remove silkscreen over vias and better positioning of some designators
2026-03-04 small grounding improvement set C9 GND pad to solid pad connection
2026-03-04 Add schematic pdf
2026-03-05 Add pinout figure for rev2a
2026-03-05 Update README.md
    Add Rev 2A BOM and pin assignment figure.
